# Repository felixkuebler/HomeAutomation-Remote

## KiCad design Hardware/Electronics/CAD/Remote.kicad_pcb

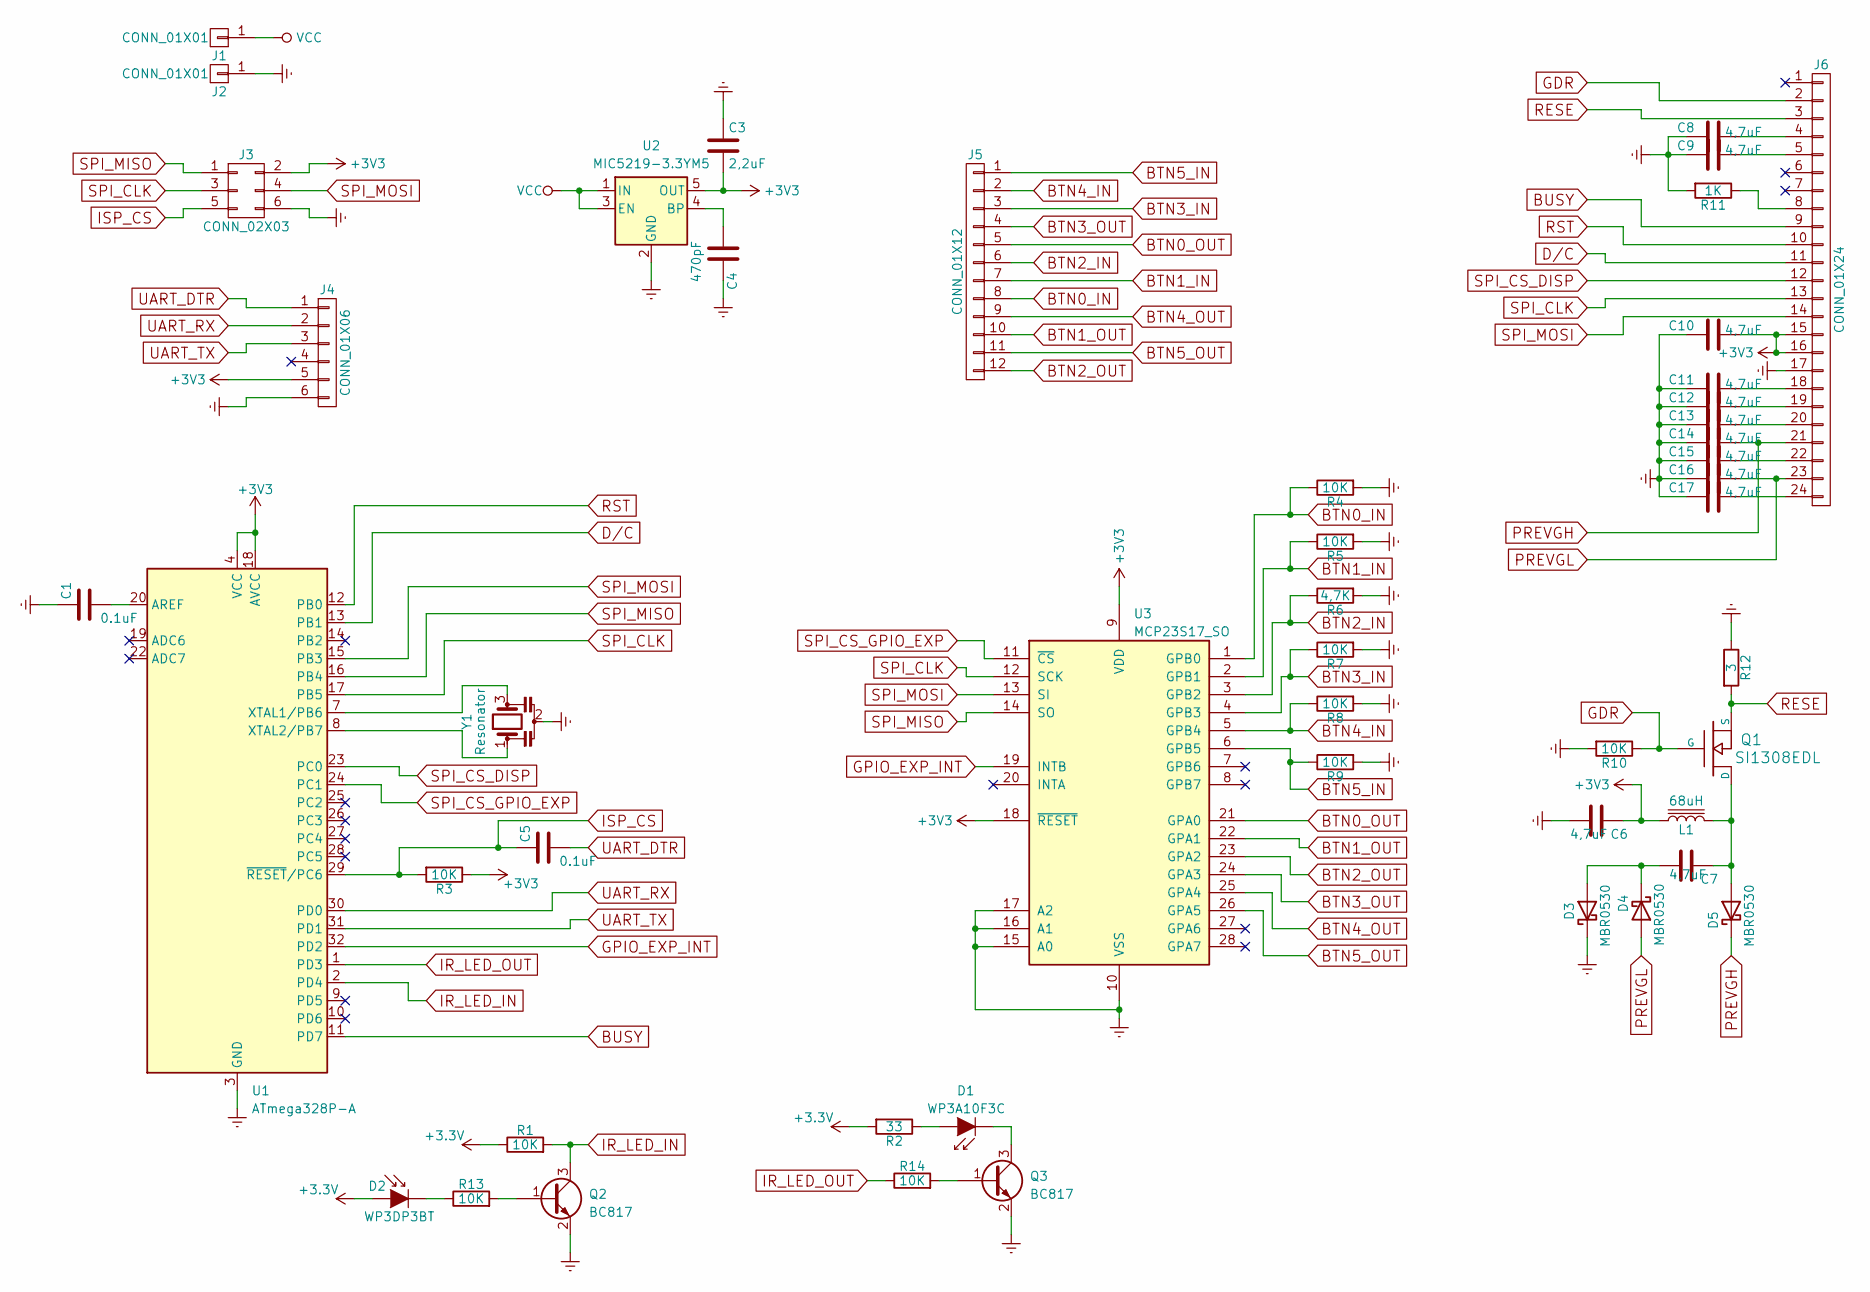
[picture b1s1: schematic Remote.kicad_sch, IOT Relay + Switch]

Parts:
C1, C5: 0.1uF; C_0805_2012Metric
C3: 2,2uF; C_0805_2012Metric
C4: 470pF; C_0805_2012Metric
C6, C7, C8, C9, C10, C11, C12, C13, C14, C15, C16, C17: 4,7uF; C_0805_2012Metric
D1: WP3A10F3C; LED_D3.0mm_Horizontal_O6.35mm_Z2.0mm
D2: WP3DP3BT; LED_D3.0mm_Horizontal_O6.35mm_Z2.0mm
D3, D4, D5: MBR0530; D_SOD-123
J1, J2: CONN_01X01; 1Pin
J3: CONN_02X03; PinHeader_2x03_P2.54mm_Vertical
J4: CONN_01X06; PinHeader_1x06_P2.54mm_Vertical
J5: CONN_01X12; SolderPad_1x12_1.27mm
J6: CONN_01X24; Hirose_FH12-24S-0.5SH_1x24-1MP_P0.50mm_Horizontal
L1: 68uH; L_1210_3225Metric
Q1: SI1308EDL; SOT-323_SC-70
Q2, Q3: BC817; SOT-23
R1, R3, R4, R5, R7, R8, R9, R10, R13, R14: 10K; R_0805_2012Metric
R2: 33; R_0805_2012Metric
R6: 4,7K; R_0805_2012Metric
R11: 1K; R_0805_2012Metric
R12: 3; R_0805_2012Metric
U1: ATmega328P-A; TQFP-32_7x7mm_P0.8mm
U2: MIC5219-3.3YM5; SOT-23-5
U3: MCP23S17_SO; SOIC-28W_7.5x17.9mm_P1.27mm
Y1: Resonator; Resonator_SMD_Murata_CSTxExxV-3Pin_3.0x1.1mm

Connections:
BTN0_IN: J5.8, R4.1, U3.1 (GPB0)
BTN0_OUT: J5.5, U3.21 (GPA0)
BTN1_IN: J5.7, R5.1, U3.2 (GPB1)
BTN1_OUT: J5.10, U3.22 (GPA1)
BTN2_IN: J5.6, R6.1, U3.3 (GPB2)
BTN2_OUT: J5.12, U3.23 (GPA2)
BTN3_IN: J5.3, R7.1, U3.4 (GPB3)
BTN3_OUT: J5.4, U3.24 (GPA3)
BTN4_IN: J5.2, R8.1, U3.5 (GPB4)
BTN4_OUT: J5.9, U3.25 (GPA4)
BTN5_IN: J5.1, R9.1, U3.6 (GPB5)
BTN5_OUT: J5.11, U3.26 (GPA5)
BUSY: J6.9, U1.11 (PD7)
D/C: J6.11, U1.13 (PB1)
Earth: C1.1, C3.1, C4.1, C6.2, C8.1, C9.1, C10.1, C11.1, C12.1, C13.1, C14.1, C15.1, C16.1, C17.1, D3.1 (K), J2.1, J3.6, J4.6, J6.17, Q2.2 (E), Q3.2 (E), R4.2, R5.2, R6.2, R7.2, R8.2, R9.2, R10.2, R11.2, R12.1, U1.3 (GND), U1.5 (GND), U1.21 (GND), U2.2 (GND), U3.10 (VSS), U3.15 (A0), U3.16 (A1), U3.17 (A2), Y1.2
GDR: J6.2, Q1.1 (G), R10.1
GPIO_EXP_INT: U1.32 (PD2), U3.19 (INTB)
IR_LED_IN: Q2.3 (C), R1.2, U1.2 (PD4)
IR_LED_OUT: R14.1, U1.1 (PD3)
ISP_CS: C5.1, J3.5, R3.2, U1.29 (~RESET/PC6)
unnamed: D1.2 (A), R2.1
unnamed: D1.1 (K), Q3.3 (C)
unnamed: D2.1 (K), R13.1
unnamed: C7.2, D3.2 (A), D4.1 (K)
unnamed: C7.1, D5.2 (A), L1.2, Q1.3 (D)
unnamed: C8.2, J6.4
unnamed: C9.2, J6.5
unnamed: J6.8, R11.1
unnamed: C11.2, J6.18
unnamed: C12.2, J6.19
unnamed: C13.2, J6.20
unnamed: C15.2, J6.22
unnamed: C17.2, J6.24
unnamed: Q2.1 (B), R13.2
unnamed: Q3.1 (B), R14.2
unnamed: C1.2, U1.20 (AREF)
unnamed: U1.7 (XTAL1/PB6), Y1.3
unnamed: U1.8 (XTAL2/PB7), Y1.1
unnamed: C4.2, U2.4 (BP)
PREVGH: C14.2, D5.1 (K), J6.21
PREVGL: C16.2, D4.2 (A), J6.23
RESE: J6.3, Q1.2 (S), R12.2
RST: J6.10, U1.12 (PB0)
SPI_CLK: J3.3, J6.13, U1.17 (PB5), U3.12 (SCK)
SPI_CS_DISP: J6.12, U1.23 (PC0)
SPI_CS_GPIO_EXP: U1.24 (PC1), U3.11 (~CS)
SPI_MISO: J3.1, U1.16 (PB4), U3.14 (SO)
SPI_MOSI: J3.4, J6.14, U1.15 (PB3), U3.13 (SI)
UART_DTR: C5.2, J4.1
UART_RX: J4.2, U1.30 (PD0)
UART_TX: J4.3, U1.31 (PD1)
VCC: J1.1, U2.1 (IN), U2.3 (EN)

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
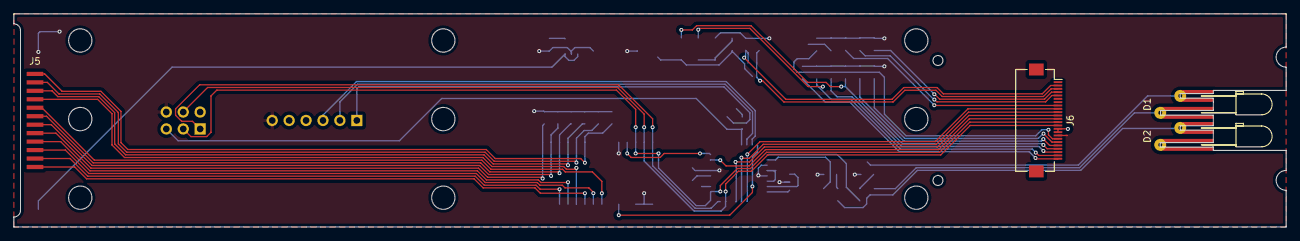
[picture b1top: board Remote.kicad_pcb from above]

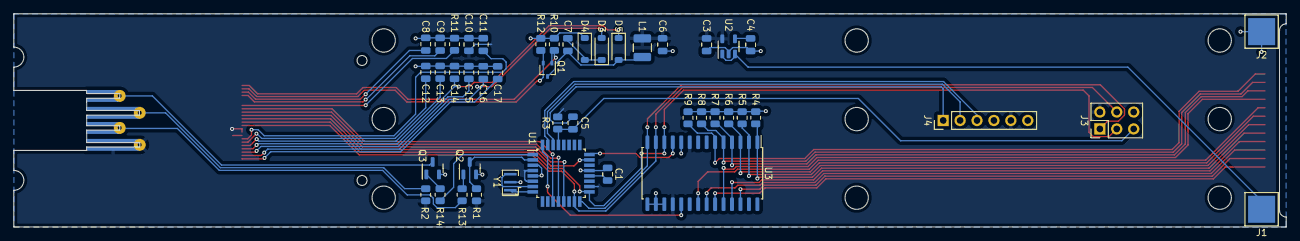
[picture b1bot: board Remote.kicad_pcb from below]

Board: 2 copper layers, 191.0 x 32.0 mm, 49 parts (45 on the bottom side), 53 nets.

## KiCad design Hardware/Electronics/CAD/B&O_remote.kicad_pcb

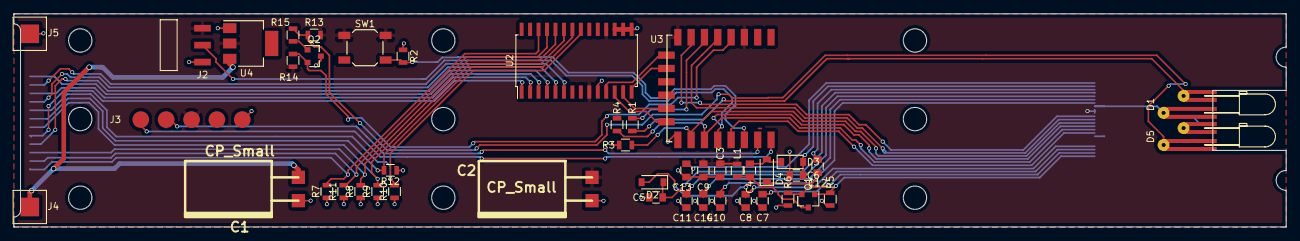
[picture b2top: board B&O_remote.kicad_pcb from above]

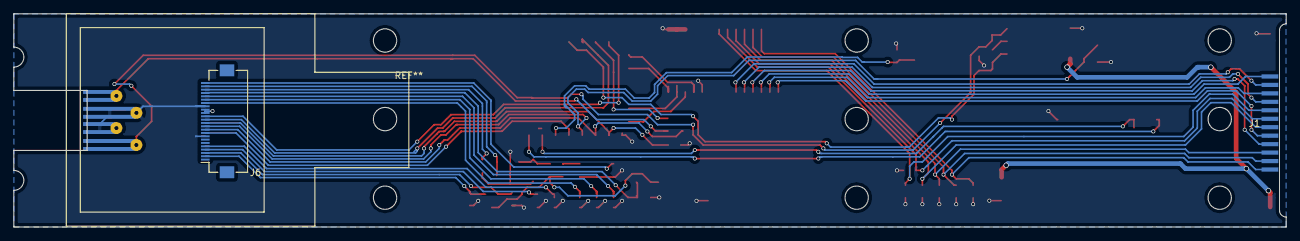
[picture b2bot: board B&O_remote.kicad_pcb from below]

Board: 2 copper layers, 191.0 x 32.0 mm, 47 parts (2 on the bottom side), 46 nets.

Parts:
C1, C2: CP_Small; CP_8x11.5mm_hor
C3: 4.7uF; C_0805
C4, C5, C6, C7, C8, C9, C10, C11, C12, C13, C14: 1uF; C_0805
D1: IR204A; LED_D3.0mm_Horizontal_O6.35mm_Z2.0mm
D2, D3, D4: MBR0520; D_SOD-123
D5: SFH203FA; LED_D3.0mm_Horizontal_O6.35mm_Z2.0mm
J1: CONN_01X12; SolderPad_1x12_1.27mm
J2: CONN_01X03; Pin_Header_SMD_1x3_Angled_2.54mm
J3: CONN_01X05; SolderPad_1x5_3.81mm
J4, J5: CONN_01X01; 1Pin
J6: CONN_01X24; Hirose_FH12-24S-0.5SH_1x24-1MP_P0.50mm_Horizontal
L1: 68uH; L_0805
Q1: AO3418; SOT-23
Q2: Q_NPN_BCE; SOT-23
R1: 330; R_0805
R2: RND 0805 1 10K; R_0805
R3, R4, R5, R7, R8, R9, R10, R11, R12, R13, R14: 10K; R_0805
R6: 3; R_0805
R15: 1K; R_0805
SW1: SW_DPST_x2; SW_SPST_SKQG
U2: MCP23S17; SOIC-28W_7.5x17.9mm_Pitch1.27mm
U3: ESP-12E; ESP-12E_SMD
U4: LD1117S33CTR; SOT-223

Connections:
BUSY: J6.9, U3.13
CLK: J6.13, U3.5
CS: J6.12, R3.2, U3.10
D/C: J2.2, J6.11, U3.12
DIN: J6.14, U3.7
GDR: J6.2, Q1.1, R5.1
GND: C1.2, C2.2, C3.1, C5.2, C6.2, C7.1, C8.1, C9.1, C10.1, C11.1, C12.1, C13.1, C14.1, D1.1, D4.1, D5.2, J2.3, J3.5, J5.1, J6.8, J6.17, Q2.3, R2.1, R3.1, R5.2, R6.2, R7.1, R8.1, R9.1, R10.1, R11.1, R12.1, U2.10, U2.15, U2.16, U2.17, U3.9, U4.1
unnamed: C1.1, J4.1, U4.3
unnamed: C4.1, D3.1, D4.2
unnamed: C4.2, D2.2, L1.1, Q1.3
unnamed: D1.2, R1.2
unnamed: D5.1, R13.2, R15.2
unnamed: J1.1, R7.2, U2.26
unnamed: J1.2, R11.2, U2.25
unnamed: J1.3, R8.2, U2.24
unnamed: J1.4, U2.4
unnamed: J1.5, U2.1
unnamed: J1.6, R9.2, U2.23
unnamed: J1.7, R12.2, U2.22
unnamed: J1.8, R10.2, U2.21
unnamed: J1.9, U2.5
unnamed: J1.10, U2.2
unnamed: J1.11, U2.6
unnamed: J1.12, U2.3
unnamed: Q2.1, R15.1
unnamed: Q2.2, R14.2, U3.4
unnamed: R1.1, U3.6
unnamed: U2.11, U3.17
unnamed: U2.12, U3.22
unnamed: U2.13, U3.21
unnamed: U2.14, U3.18
PREVGH: C5.1, D2.1, J6.21
PREVGL: C6.1, D3.2, J6.23
RES#: J6.10, R4.2, U3.11
RESE: J6.3, Q1.2, R6.1
RESET: R2.2, SW1.2, U3.14
RX: J3.2, U3.15
TX: J3.1, U3.16
VCI: C2.1, C3.2, C9.2, J2.1, J3.3, J6.15, J6.16, L1.2, R4.1, R13.1, R14.1, SW1.1, U2.9, U2.18, U3.3, U3.8, U4.2
VCOM: C13.2, J6.24
VDD: C10.2, J6.18
VGH: C8.2, J6.5
VGL: C7.2, J6.4
VPP: C14.2, J6.19
VSH: C11.2, J6.20
VSL: C12.2, J6.22

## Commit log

2018-09-20 initial setup
2018-09-20 cleanup
2019-02-21 status check and refactoring
2022-10-22 rename Specifications to Datasheets
2022-10-23 rename software source and move tests in source
2022-10-23 rename tests
2023-03-27 update design
2023-03-27 update datasheets
2023-03-27 generated files
2023-04-13 add datasheets
2023-04-13 version 1.0 of remote schematics and pcb
2023-04-13 add gerber files
2023-04-13 add 3d object for FFC connector
2023-05-15 fix expander in schematics and pcb design
2023-05-15 Add MCP interrupthandling
2023-05-15 add display text feature and remove unnecessary display driver files
2023-05-15 add gpio expander software test
2023-05-15 add B&O keybad test
2023-05-15 Add simple code for version 1.0 hardware test
2023-05-15 Add deep sleep function to save power
2023-05-15 move Keypad constants to program memory
2023-05-15 Remove unused test setup
2023-05-15 remove old kicad project
2023-05-15 add epaper software test
2023-05-15 Add IR Commands
2023-05-15 add software first draft
2023-05-15 Code cleanup
2023-05-16 Change IR test name
2023-05-17 First working IR remote with basic features
2023-05-17 Change IR led resistor from 330 to 33 Ohm
2023-05-17 Add code to convert IR proton code to raw code
2023-05-17 Use raw IR code for tv on/off
2024-11-21 move gerber files to location outside of CAD
